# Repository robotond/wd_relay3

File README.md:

# wd_relay3
Highlights:
MCU platform: STM32G070CBT6
On board switching power supply with XL1509-ADJ
RS-485 interface
2 pcs of safety DPDT relays with hardware watchdog timers (SN74AHC123)
1 pc DPDT relay.
MAX 24V DC only
HW: KiCAD project with schematics, PCB, gerbers
SW: STM32CUBEIDE Version: 1.12.1 Build: 16088_20230420_1057 (UTC)

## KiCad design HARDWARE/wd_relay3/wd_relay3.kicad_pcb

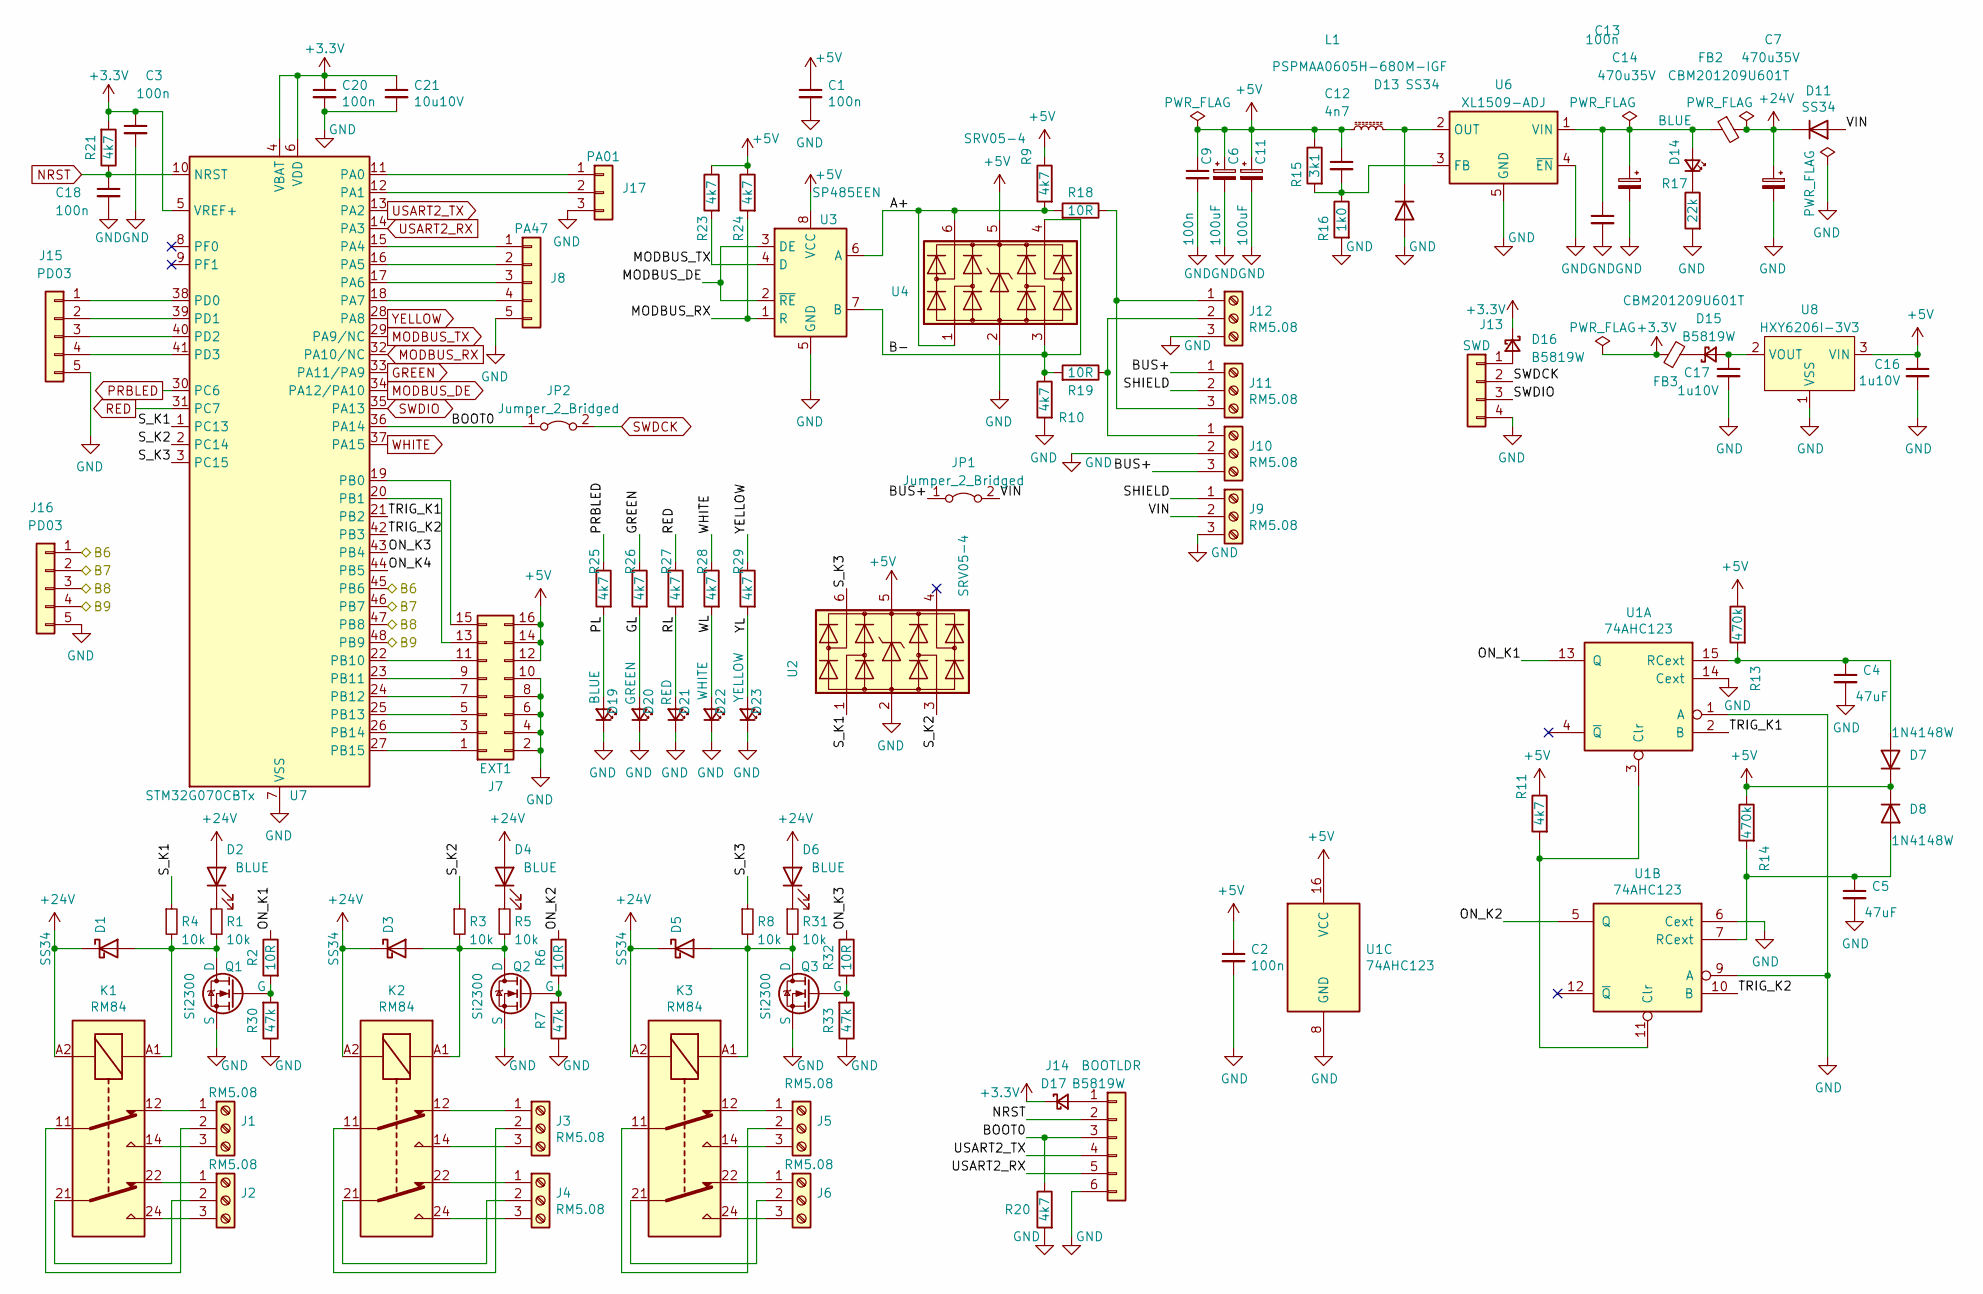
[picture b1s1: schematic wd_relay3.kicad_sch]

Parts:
C1, C2, C3, C9, C13, C18, C20: 100n; C_0603_1608Metric; LCSC C14663
C4, C5: 47uF; C_0805_2012Metric; LCSC C16780
C6, C11: 100uF; CP_Elec_5x5.4; LCSC C191859
C7, C14: 470u35V; CP_Elec_10x10.5; LCSC C976030
C12: 4n7; C_0603_1608Metric_Pad1.08x0.95mm_HandSolder; LCSC C696859
C16, C17: 1u10V; C_0603_1608Metric_Pad1.08x0.95mm_HandSolder; LCSC C59782
C21: 10u10V; C_0603_1608Metric; LCSC C32635
D1, D3, D5, D11, D13: SS34; D_SMA; LCSC C8678
D2, D4, D6, D14, D19: BLUE; LED_0603_1608Metric_Pad1.05x0.95mm_HandSolder; LCSC C965807
D7, D8: 1N4148W; D_SOD-123; LCSC C81598
D15, D16, D17: B5819W; D_SOD-123; LCSC C2943878
D20: GREEN; LED_0603_1608Metric_Pad1.05x0.95mm_HandSolder; LCSC C965805
D21: RED; LED_0603_1608Metric_Pad1.05x0.95mm_HandSolder; LCSC C965799
D22: WHITE; LED_0603_1608Metric_Pad1.05x0.95mm_HandSolder; LCSC C965808
D23: YELLOW; LED_0603_1608Metric_Pad1.05x0.95mm_HandSolder; LCSC C965802
FB2, FB3: CBM201209U601T; L_0805_2012Metric_Pad1.15x1.40mm_HandSolder; LCSC C139168
J1, J2, J3, J4, J5, J6, J9, J10, J11, J12: RM5.08; TerminalBlock_bornier-3_P5.08mm
J7: EXT1; PinHeader_2x08_P2.54mm_Vertical
J8: PA47; JST_XH_B5B-XH-A_1x05_P2.50mm_Vertical
J13: SWD; JST_XH_B4B-XH-A_1x04_P2.50mm_Vertical
J14: BOOTLDR; JST_XH_B6B-XH-A_1x06_P2.50mm_Vertical
J15, J16: PD03; JST_XH_B5B-XH-A_1x05_P2.50mm_Vertical
J17: PA01; JST_XH_B3B-XH-A_1x03_P2.50mm_Vertical
JP1, JP2: Jumper_2_Bridged; SolderJumper-2_P1.3mm_Bridged2Bar_Pad1.0x1.5mm
K1, K2, K3: RM84; Relay_DPDT_Finder_40.52
L1: PSPMAA0605H-680M-IGF; L_6.6x7.1_H3; LCSC C2983094
Q1, Q2, Q3: Si2300; SOT-23_GSD; LCSC C347480
R1, R3, R4, R5, R8, R31: 10k; R_0603_1608Metric_Pad0.98x0.95mm_HandSolder; LCSC C25804
R2, R6, R18, R19, R32: 10R; R_0603_1608Metric_Pad0.98x0.95mm_HandSolder; LCSC C2906983
R7, R30, R33: 47k; R_0603_1608Metric_Pad0.98x0.95mm_HandSolder; LCSC C25819
R9, R10, R11, R20, R21, R23, R24, R25, R26, R27, R28, R29: 4k7; R_0603_1608Metric_Pad0.98x0.95mm_HandSolder; LCSC C23162
R13, R14: 470k; R_0603_1608Metric_Pad0.98x0.95mm_HandSolder; LCSC C23178
R15: 3k1; R_0603_1608Metric_Pad0.98x0.95mm_HandSolder; LCSC C2924132
R16: 1k0; R_0603_1608Metric_Pad0.98x0.95mm_HandSolder; LCSC C2907113
R17: 22k; R_0603_1608Metric_Pad0.98x0.95mm_HandSolder; LCSC C2907015
U1: 74AHC123; SOIC-16_3.9x9.9mm_P1.27mm; LCSC C554214
U2, U4: SRV05-4; SOT-23-6_Handsoldering; LCSC C2836319
U3: SP485EEN; SOIC-8_3.9x4.9mm_P1.27mm; LCSC C6855
U6: XL1509-ADJ; SOIC-8_3.9x4.9mm_P1.27mm; LCSC C74192
U7: STM32G070CBTx; LQFP-48_7x7mm_P0.5mm; LCSC C529338
U8: HXY6206I-3V3; SOT-23; LCSC C5148688

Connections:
+3.3V: C3.1, C20.1, C21.1, D16.1 (K), D17.1 (K), FB3.1, R21.2, U7.4 (VBAT), U7.5 (VREF+), U7.6 (VDD)
+5V: C1.1, C2.1, C6.1, C9.1, C11.1, C12.1, C16.1, D7.1 (K), D8.1 (K), J7.12, J7.14, J7.16, L1.1, R9.1, R11.1, R13.1, R14.1, R15.1, R23.1, R24.1, U1.16 (VCC), U2.5 (VP), U3.8 (VCC), U4.5 (VP), U8.3 (VIN)
+24V: C7.1, D1.1 (K), D2.2 (A), D3.1 (K), D4.2 (A), D5.1 (K), D6.2 (A), D11.1 (K), FB2.2, K1.A2, K2.A2, K3.A2
/A+: R9.2, R18.2, U3.6 (A), U4.1 (I/O1), U4.6 (I/O4)
/B6: J16.1, U7.45 (PB6)
/B7: J16.2, U7.46 (PB7)
/B8: J16.3, U7.47 (PB8)
/B9: J16.4, U7.48 (PB9)
/B-: R10.1, R19.2, U3.7 (B), U4.3 (I/O3), U4.4 (I/O4)
/BOOT0: J14.3, JP2.1 (A), R20.1, U7.36 (PA14)
/BUS+: J10.3, J11.1, JP1.1 (A)
/GL: D20.2 (A), R26.2
/ON_K1: R2.1, U1.13 (Q)
/ON_K2: R6.1, U1.5 (Q)
/ON_K3: R32.1, U7.43 (PB4)
/ON_K4: U7.44 (PB5)
/PL: D19.2 (A), R25.2
/RL: D21.2 (A), R27.2
/SHIELD: J9.1, J11.2
/S_K1: R4.1, U2.1 (I/O1), U7.1 (PC13)
/S_K2: R3.1, U2.3 (I/O3), U7.2 (PC14)
/S_K3: R8.1, U2.6 (I/O4), U7.3 (PC15)
/TRIG_K1: U1.2 (B), U7.21 (PB2)
/TRIG_K2: U1.10 (B), U7.42 (PB3)
/VIN: D11.2 (A), J9.2, JP1.2 (B)
/WL: D22.2 (A), R28.2
/YL: D23.2 (A), R29.2
GND: C1.2, C2.2, C3.2, C4.2, C5.2, C6.2, C7.2, C9.2, C11.2, C13.2, C14.2, C16.2, C17.2, C18.2, C20.2, C21.2, D13.2 (A), D19.1 (K), D20.1 (K), D21.1 (K), D22.1 (K), D23.1 (K), J7.2, J7.4, J7.6, J7.8, J7.10, J8.5, J9.3, J10.2, J12.3, J13.4, J14.6, J15.5, J16.5, J17.3, Q1.2 (S), Q2.2 (S), Q3.2 (S), R7.1, R10.2, R16.2, R17.2, R20.2, R30.1, R33.1, U1.1 (A), U1.6 (Cext), U1.8 (GND), U1.9 (A), U1.14 (Cext), U2.2 (VN), U3.5 (GND), U4.2 (VN), U6.4 (~EN), U6.5 (GND), U6.6 (GND), U6.7 (GND), U6.8 (GND), U7.7 (VSS), U8.1 (VSS)
GREEN: R26.1, U7.33 (PA11/PA9)
MODBUS_DE: U3.2 (~RE), U3.3 (DE), U7.34 (PA12/PA10)
MODBUS_RX: R24.2, U3.1 (R), U7.32 (PA10/NC)
MODBUS_TX: R23.2, U3.4 (D), U7.29 (PA9/NC)
NRST: C18.1, J14.2, R21.1, U7.10 (NRST)
unnamed: C13.1, C14.1, D14.2 (A), FB2.1, U6.1 (VIN)
unnamed: D1.2 (A), K1.A1, Q1.3 (D), R1.2, R4.2
unnamed: D2.1 (K), R1.1
unnamed: D3.2 (A), K2.A1, Q2.3 (D), R3.2, R5.2
unnamed: D4.1 (K), R5.1
unnamed: D5.2 (A), K3.A1, Q3.3 (D), R8.2, R31.2
unnamed: D6.1 (K), R31.1
unnamed: C4.1, D7.2 (A), R13.2, U1.15 (RCext)
unnamed: C5.1, D8.2 (A), R14.2, U1.7 (RCext)
unnamed: D13.1 (K), L1.2, U6.2 (OUT)
unnamed: D14.1 (K), R17.1
unnamed: C17.1, D15.2 (A), U8.2 (VOUT)
unnamed: D15.1 (K), FB3.2
unnamed: D16.2 (A), J13.1
unnamed: D17.2 (A), J14.1
unnamed: J1.1, K1.12
unnamed: J1.2, K1.11
unnamed: J1.3, K1.14
unnamed: J2.1, K1.22
unnamed: J2.2, K1.21
unnamed: J2.3, K1.24
unnamed: J3.1, K2.12
unnamed: J3.2, K2.11
unnamed: J3.3, K2.14
unnamed: J4.1, K2.22
unnamed: J4.2, K2.21
unnamed: J4.3, K2.24
unnamed: J5.1, K3.12
unnamed: J5.2, K3.11
unnamed: J5.3, K3.14
unnamed: J6.1, K3.22
unnamed: J6.2, K3.21
unnamed: J6.3, K3.24
unnamed: J7.1, U7.27 (PB15)
unnamed: J7.3, U7.26 (PB14)
unnamed: J7.5, U7.25 (PB13)
unnamed: J7.7, U7.24 (PB12)
unnamed: J7.9, U7.23 (PB11)
unnamed: J7.11, U7.22 (PB10)
unnamed: J7.13, U7.20 (PB1)
unnamed: J7.15, U7.19 (PB0)
unnamed: J8.1, U7.15 (PA4)
unnamed: J8.2, U7.16 (PA5)
unnamed: J8.3, U7.17 (PA6)
unnamed: J8.4, U7.18 (PA7)
unnamed: J10.1, J12.2, R19.1
unnamed: J11.3, J12.1, R18.1
unnamed: J15.1, U7.38 (PD0)
unnamed: J15.2, U7.39 (PD1)
unnamed: J15.3, U7.40 (PD2)
unnamed: J15.4, U7.41 (PD3)
unnamed: J17.1, U7.11 (PA0)
unnamed: J17.2, U7.12 (PA1)
unnamed: Q1.1 (G), R2.2, R30.2
unnamed: Q2.1 (G), R6.2, R7.2
unnamed: Q3.1 (G), R32.2, R33.2
unnamed: R11.2, U1.3 (Clr), U1.11 (Clr)
unnamed: C12.2, R15.2, R16.1, U6.3 (FB)
PRBLED: R25.1, U7.30 (PC6)
RED: R27.1, U7.31 (PC7)
SWDCK: J13.2, JP2.2 (B)
SWDIO: J13.3, U7.35 (PA13)
USART2_RX: J14.5, U7.14 (PA3)
USART2_TX: J14.4, U7.13 (PA2)
WHITE: R28.1, U7.37 (PA15)
YELLOW: R29.1, U7.28 (PA8)

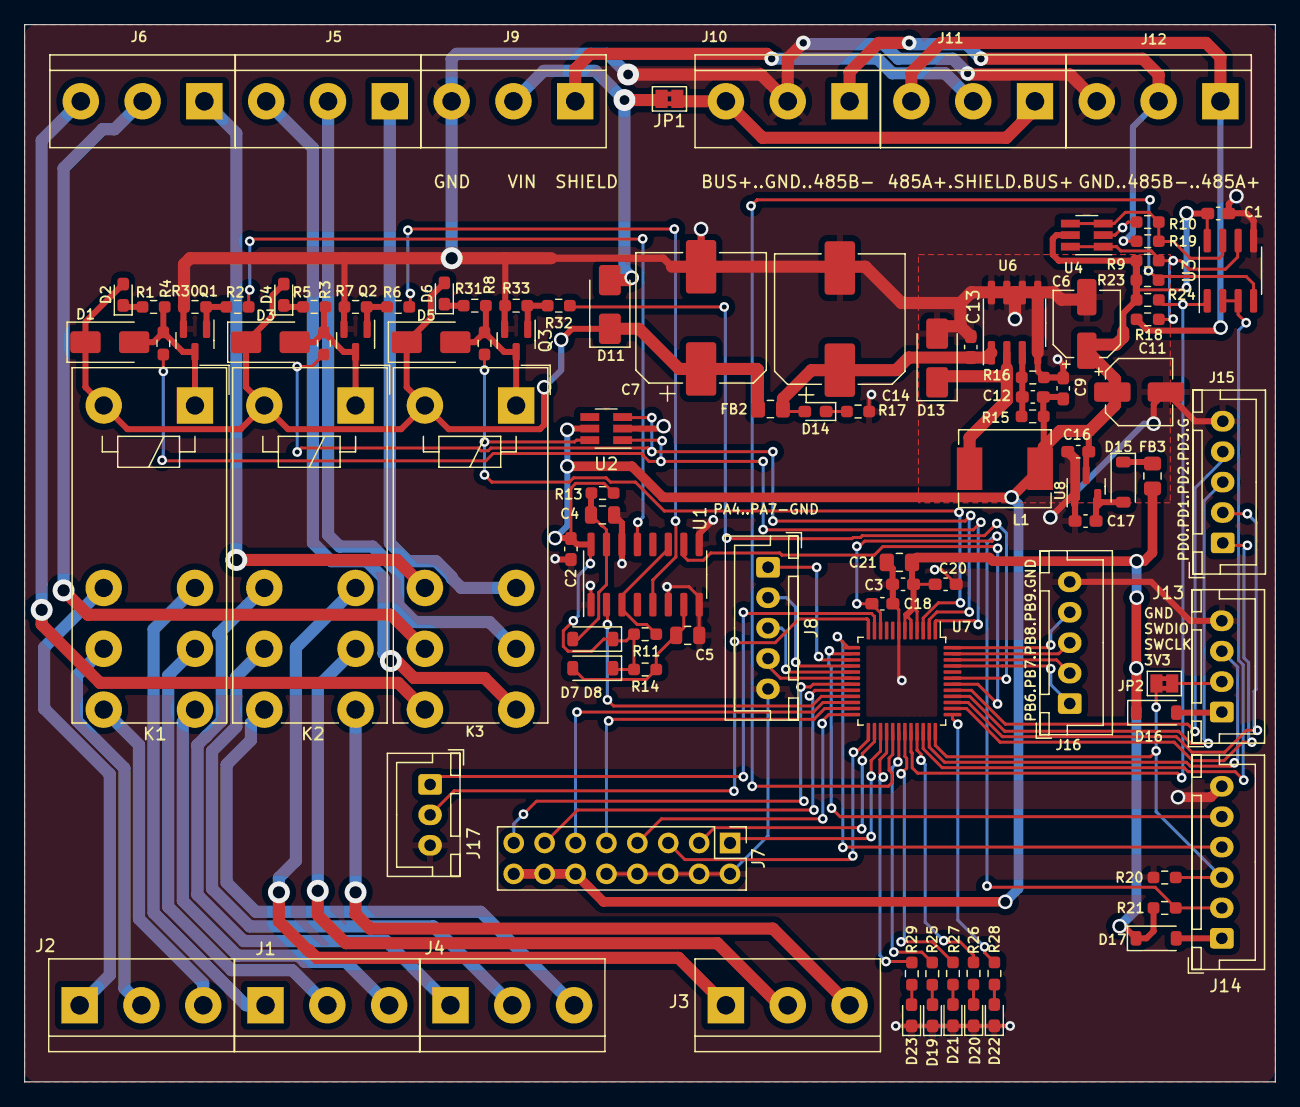
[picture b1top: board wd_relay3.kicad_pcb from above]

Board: 2 copper layers, 102.8 x 86.9 mm, 102 parts (0 on the bottom side), 98 nets.

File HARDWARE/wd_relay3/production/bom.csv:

Designator,Footprint,Quantity,Value,LCSC Part #
"C1, C13, C18, C2, C20, C3, C9",0603,7,100n,C14663
"C11, C6",CP_Elec_5x5.4,2,100uF,C191859
C12,0603,1,4n7,C696859
"C14, C7",CP_Elec_10x10.5,2,470u35V,C976030
"C16, C17",0603,2,1u10V,C59782
C21,0805,1,10u10V,C32635
"C4, C5",0805,2,47uF,C16780
"D1, D11, D13, D3, D5",D_SMA,5,SS34,C8678
"D14, D19, D2, D4, D6",0603,5,BLUE,C965807
"D15, D16, D17",D_SOD-123,3,B5819W,C2943878
D20,0603,1,GREEN,C965805
D21,0603,1,RED,C965799
D22,0603,1,WHITE,C965808
D23,0603,1,YELLOW,C965802
"D7, D8",D_SOD-123,2,1N4148W,C81598
"FB2, FB3",0805,2,CBM201209U601T,C139168
"J1, J10, J11, J12, J2, J3, J4, J5, J6, J9",TerminalBlock_bornier-3_P5.08mm,10,RM5.08,
J13,JST_XH_B4B-XH-A_1x04_P2.50mm_Vertical,1,SWD,
J14,JST_XH_B6B-XH-A_1x06_P2.50mm_Vertical,1,BOOTLDR,
"J15, J16",JST_XH_B5B-XH-A_1x05_P2.50mm_Vertical,2,PD03,
J17,JST_XH_B3B-XH-A_1x03_P2.50mm_Vertical,1,PA01,
J7,PinHeader_2x08_P2.54mm_Vertical,1,EXT1,
J8,JST_XH_B5B-XH-A_1x05_P2.50mm_Vertical,1,PA47,
"JP1, JP2",SolderJumper-2_P1.3mm_Bridged2Bar_Pad1.0x1.5mm,2,Jumper_2_Bridged,
"K1, K2, K3",Relay_DPDT_Finder_40.52,3,RM84,
L1,L_6.6x7.1_H3,1,PSPMAA0605H-680M-IGF,C2983094
"Q1, Q2, Q3",SOT-23_GSD,3,Si2300,C347480
"R1, R3, R31, R4, R5, R8",0603,6,10k,C25804
"R10, R11, R20, R21, R23, R24, R25, R26, R27, R28, R29, R9",0603,12,4k7,C23162
"R13, R14",0603,2,470k,C23178
R15,0603,1,3k1,C2924132
R16,0603,1,1k0,C2907113
R17,0603,1,22k,C2907015
"R18, R19, R2, R32, R6",0603,5,10R,C2906983
"R30, R33, R7",0603,3,47k,C25819
U1,SOIC-16_3.9x9.9mm_P1.27mm,1,74AHC123,C554214
"U2, U4",SOT-23-6_Handsoldering,2,SRV05-4,C2836319
U3,SOIC-8_3.9x4.9mm_P1.27mm,1,SP485EEN,C6855
U6,SOIC-8_3.9x4.9mm_P1.27mm,1,XL1509-ADJ,C74192
U7,LQFP-48_7x7mm_P0.5mm,1,STM32G070CBTx,C529338
U8,SOT-23,1,HXY6206I-3V3,C5148688

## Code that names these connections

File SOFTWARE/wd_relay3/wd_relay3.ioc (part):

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Mcu.Name=STM32G070CBTx
Mcu.Package=LQFP48
Mcu.UserName=STM32G070CBTx
PA0.GPIOParameters=GPIO_Label
PA0.GPIO_Label=PA0
PA0.Signal=GPIO_Output
PA1.GPIOParameters=GPIO_Label
PA1.GPIO_Label=PA1
PA1.Signal=GPIO_Output
PA10.Mode=Asynchronous
PA10.Signal=USART1_RX
PA11\ [PA9].GPIOParameters=GPIO_Label
PA11\ [PA9].GPIO_Label=GREEN
PA11\ [PA9].Signal=GPIO_Output
PA12\ [PA10].Mode=Hardware Flow Control (RS485)
PA12\ [PA10].Signal=USART1_DE
PA13.Mode=Serial_Wire
PA13.Signal=SYS_SWDIO
PA14-BOOT0.Mode=Serial_Wire
PA14-BOOT0.Signal=SYS_SWCLK
PA15.GPIOParameters=GPIO_Label
PA15.GPIO_Label=WHITE
PA15.Signal=GPIO_Output
PA2.Mode=Asynchronous
PA2.Signal=USART2_TX
PA3.Mode=Asynchronous
PA3.Signal=USART2_RX
PA4.GPIOParameters=GPIO_Label
PA4.GPIO_Label=PA4
PA4.Signal=GPIO_Output
PA5.GPIOParameters=GPIO_Label
PA5.GPIO_Label=PA5
PA5.Signal=GPIO_Output
PA6.GPIOParameters=GPIO_Label
PA6.GPIO_Label=PA6
PA6.Signal=GPIO_Output
PA7.GPIOParameters=GPIO_Label
PA7.GPIO_Label=PA7
PA7.Signal=GPIO_Output
PA8.GPIOParameters=GPIO_Label
PA8.GPIO_Label=YELLOW
PA8.Signal=GPIO_Output
PA9.Mode=Asynchronous
PA9.Signal=USART1_TX
PB0.GPIOParameters=GPIO_Label
PB0.GPIO_Label=PB0
PB0.Signal=GPIO_Output
PB1.GPIOParameters=GPIO_Label
PB1.GPIO_Label=PB1
PB1.Signal=GPIO_Output
PB10.GPIOParameters=GPIO_Label
PB10.GPIO_Label=PB10
PB10.Signal=GPIO_Output
PB11.GPIOParameters=GPIO_Label
PB11.GPIO_Label=PB11
PB11.Signal=GPIO_Output
PB12.GPIOParameters=GPIO_Label
PB12.GPIO_Label=PB12
PB12.Signal=GPIO_Output
PB13.GPIOParameters=GPIO_Label
PB13.GPIO_Label=PB13
PB13.Signal=GPIO_Output
PB14.GPIOParameters=GPIO_Label
PB14.GPIO_Label=PB14
PB14.Signal=GPIO_Output
PB15.GPIOParameters=GPIO_Label
PB15.GPIO_Label=PB15
PB15.Signal=GPIO_Output
PB2.GPIOParameters=GPIO_Label
PB2.GPIO_Label=TRIG_K1
PB2.Signal=GPIO_Output
PB3.GPIOParameters=GPIO_Label
PB3.GPIO_Label=TRIG_K2
PB3.Signal=GPIO_Output
PB4.GPIOParameters=GPIO_Label
PB4.GPIO_Label=ON_K3
PB4.Signal=GPIO_Output
PB5.GPIOParameters=GPIO_Label
PB5.GPIO_Label=PB5
PB5.Signal=GPIO_Output
PB6.GPIOParameters=GPIO_Label
PB6.GPIO_Label=PB6
PB6.Signal=GPIO_Output
PB7.GPIOParameters=GPIO_Label
PB7.GPIO_Label=PB7
PB7.Signal=GPIO_Output
PB8.GPIOParameters=GPIO_Label
PB8.GPIO_Label=PB8
PB8.Signal=GPIO_Output
PB9.GPIOParameters=GPIO_Label
PB9.GPIO_Label=PB9
PB9.Signal=GPIO_Output
PC13.GPIOParameters=GPIO_Label
PC13.GPIO_Label=S_K1
PC13.Signal=GPIO_Input
PC14-OSC32_IN\ (PC14).GPIOParameters=GPIO_Label
PC14-OSC32_IN\ (PC14).GPIO_Label=S_K2
PC14-OSC32_IN\ (PC14).Signal=GPIO_Input
PC15-OSC32_OUT\ (PC15).GPIOParameters=GPIO_Label
PC15-OSC32_OUT\ (PC15).GPIO_Label=S_K3
PC15-OSC32_OUT\ (PC15).Signal=GPIO_Input
PC6.GPIOParameters=GPIO_Label
PC6.GPIO_Label=PRBLED
PC6.Signal=GPIO_Output
PC7.GPIOParameters=GPIO_Label
PC7.GPIO_Label=RED
PC7.Signal=GPIO_Output
PD0.GPIOParameters=GPIO_Label
PD0.GPIO_Label=PD0
PD0.Signal=GPIO_Input
PD1.GPIOParameters=GPIO_Label
PD1.GPIO_Label=PD1
PD1.Signal=GPIO_Input
PD2.GPIOParameters=GPIO_Label
PD2.GPIO_Label=PD2
PD2.Signal=GPIO_Input
PD3.GPIOParameters=GPIO_Label
PD3.GPIO_Label=PD3
PD3.Signal=GPIO_Input
RCC.HSE_VALUE=8000000
RCC.SYSCLKFreq_VALUE=64000000
RCC.SYSCLKSource=RCC_SYSCLKSOURCE_PLLCLK
board=custom

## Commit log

2023-06-29 Initial commit, added hardware and software files from local folder
2024-09-03 .gitignore file added
2024-09-04 Relay K3 periodic operation added
